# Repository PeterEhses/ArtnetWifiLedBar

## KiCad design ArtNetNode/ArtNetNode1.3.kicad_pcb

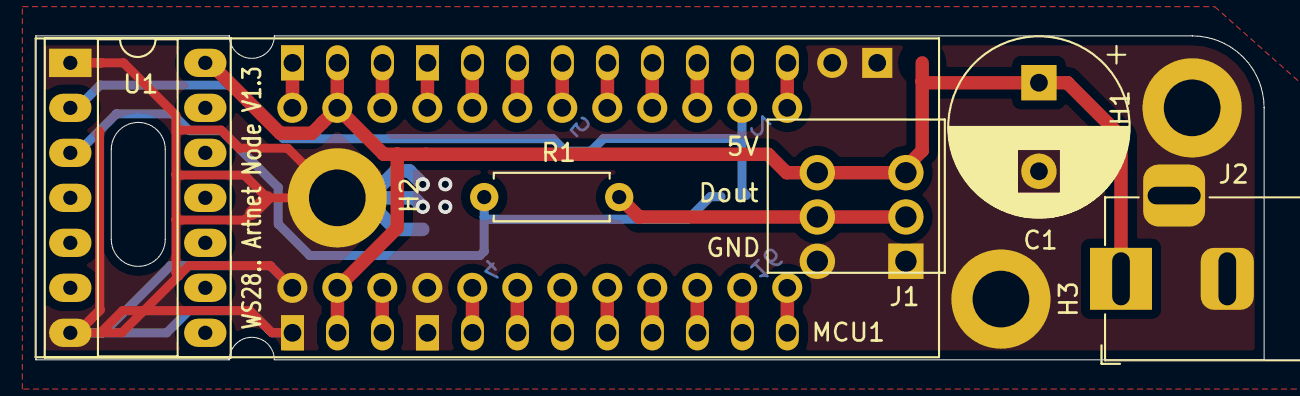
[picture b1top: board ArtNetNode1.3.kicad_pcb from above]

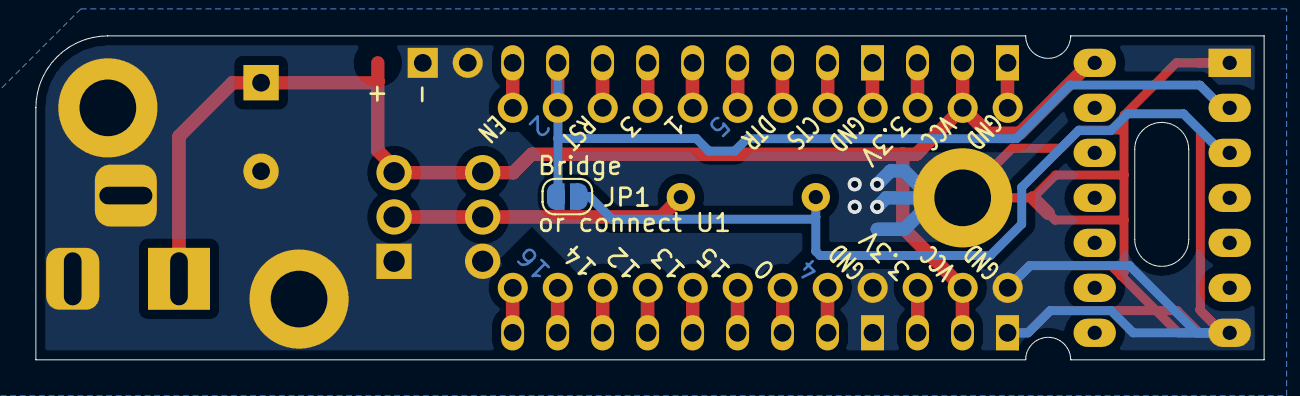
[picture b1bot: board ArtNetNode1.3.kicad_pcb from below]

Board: 2 copper layers, 69.3 x 18.3 mm, 13 parts (3 on the bottom side), 24 nets.

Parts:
14: Conn_01x12; PinHeader_1x12_P2.54mm_Vertical
-: Conn_01x02; PinSocket_1x02_P2.54mm_Vertical
C1: CP; CP_Radial_D10.0mm_P5.00mm
GND: Conn_01x12; PinHeader_1x12_P2.54mm_Vertical
H1, H2, H3: MountingHole_Pad; MountingHole_3.2mm_M3_DIN965_Pad
J1: Conn_01x03; GRUNDGEHAEUSE_PTSM_0_5__3_HHI_2_5_THR
J2: Barrel_Jack_Switch; BarrelJack_Horizontal
JP1: Jumper_NO_Small; SolderJumper-2_P1.3mm_Open_RoundedPad1.0x1.5mm
MCU1: WiFi_Kit_8; Heltec_Wifi_Kit_8
R1: 220; R_Axial_DIN0207_L6.3mm_D2.5mm_P7.62mm_Horizontal
U1: 74AHCT125; DIP-14_W7.62mm_Socket_LongPads

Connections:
/2: 14.11, -.2, C1.1, GND.2, J1.1, J2.1, MCU1.2, MCU1.21, U1.14
/3: 14.10, MCU1.3
/5: GND.10, MCU1.5
/6: 14.3, MCU1.6
/7: GND.1, MCU1.7
/8: 14.2, MCU1.8
/9: GND.12, MCU1.9
/10: 14.4, MCU1.10
/11: 14.1, MCU1.11
/12: 14.5, MCU1.12
/13: 14.6, MCU1.13
/14: GND.11, JP1.2, MCU1.14, U1.2
/15: 14.7, MCU1.15
/16: 14.8, MCU1.16
/17: GND.5, MCU1.17
/18: GND.6, MCU1.18
/19: GND.4, MCU1.19
/20: GND.3, MCU1.20
/24: GND.7, MCU1.24
/25: GND.9, MCU1.25
/26: GND.8, MCU1.26
GND: 14.9, 14.12, -.1, C1.2, H1.1, H2.1, H3.1, J1.3, J2.2, J2.3, MCU1.1, MCU1.4, U1.1, U1.7
unnamed: J1.2, R1.2
unnamed: JP1.1, R1.1, U1.3

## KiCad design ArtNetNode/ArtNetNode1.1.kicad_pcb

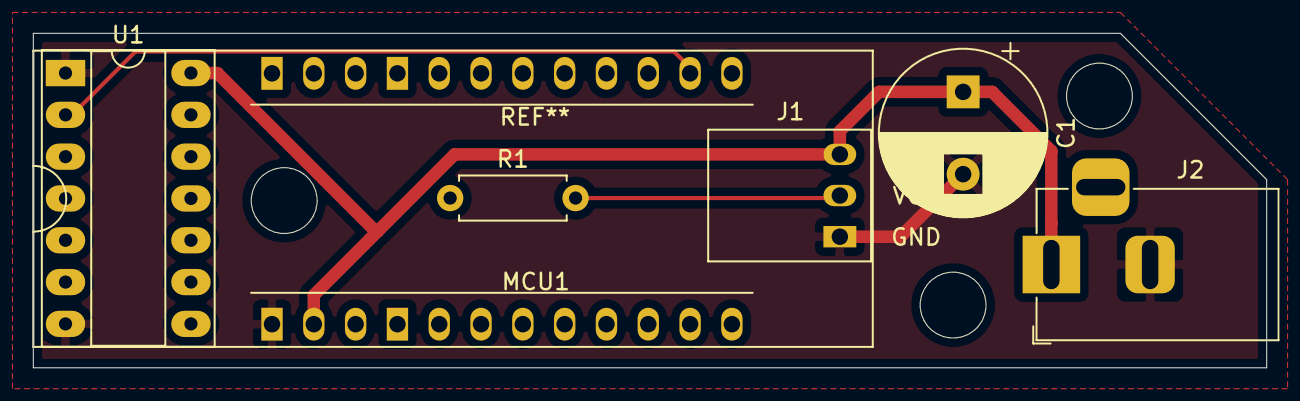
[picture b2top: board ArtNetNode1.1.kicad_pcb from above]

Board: 2 copper layers, 74.9 x 20.3 mm, 6 parts (0 on the bottom side), 5 nets.

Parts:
C1: CP; CP_Radial_D10.0mm_P5.00mm
J1: Conn_01x03; GRUNDGEHAEUSE_PTSM_0_5__3_HHI_2_5_THR
J2: Jack-DC; BarrelJack_Horizontal
MCU1: WiFi_Kit_8; Heltec_Wifi_Kit_8
R1: 220; R_Axial_DIN0207_L6.3mm_D2.5mm_P7.62mm_Horizontal
U1: 74AHCT125; DIP-14_W7.62mm_Socket_LongPads

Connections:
unnamed: C1.1, J1.1, J2.1, MCU1.2, U1.14
unnamed: C1.2, J1.3, J2.2, MCU1.1, U1.1, U1.7
unnamed: J1.2, R1.2
unnamed: MCU1.14, U1.2
unnamed: R1.1, U1.3

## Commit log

2021-01-04 KiCad + TouchDesigner Files
